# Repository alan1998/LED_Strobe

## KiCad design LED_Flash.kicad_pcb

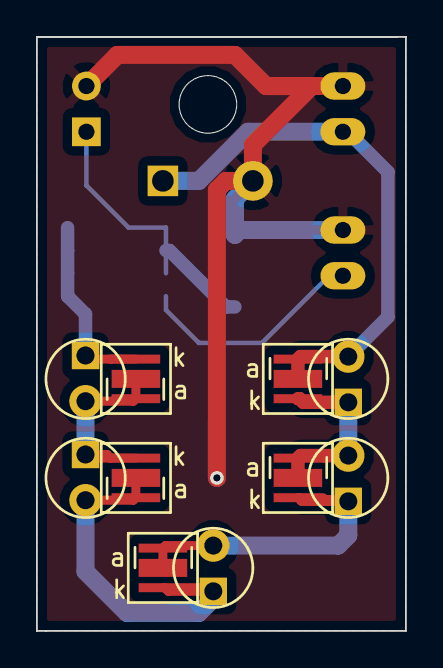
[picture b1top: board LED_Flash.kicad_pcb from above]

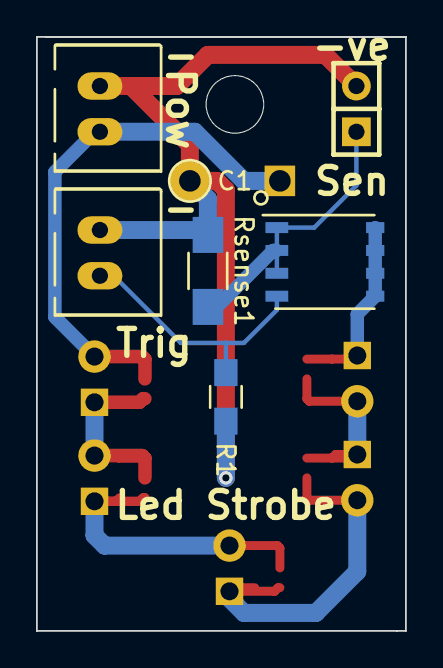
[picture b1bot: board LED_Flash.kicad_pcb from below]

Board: 2 copper layers, 20.5 x 33.0 mm, 12 parts (7 on the bottom side), 9 nets.

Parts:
C1: CP; C_Radial_P5_NoCan
D1, D2, D3, D4, D5: LED; Led-Composite
JP1: Jumper_NO_Small; Pin_Header_Straight_1x02
P1: P_In; JST-XH2
P3: Trig_In; JST-XH2
Q1: Q_NMOS_SGD; SO-8_NFET
R1: 10k; R_0805_HandSoldering
Rsense1: R100; R_1206_HandSoldering

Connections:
/Trig: P3.1, Q1.2, R1.1
/Vcc: C1.1, D1.2, P1.1
GND: C1.2, JP1.2, P1.2, P3.2, R1.2, Rsense1.2
unnamed: D1.1, D2.2
unnamed: D2.1, D3.2
unnamed: D3.1, D4.2
unnamed: D4.1, D5.2
unnamed: D5.1, Q1.3
unnamed: JP1.1, Q1.1, Rsense1.1

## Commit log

2016-10-05 Extra silk markings and change to SO-8 footprint
2016-10-05 Extra silk for notes
2016-10-12 Add some examples to schematic and part numbers
